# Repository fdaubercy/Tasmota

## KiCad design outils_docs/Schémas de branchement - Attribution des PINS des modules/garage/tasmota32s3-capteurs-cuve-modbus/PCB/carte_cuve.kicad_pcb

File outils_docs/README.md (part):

<hr></hr>

**Vous trouverez ici la méthodologie de développement de scripts en langage BERRY pour tasmota.<br/> Les différents devices développéespour la domotique du domicile sont des forks de Tasmota personnalisés.**

<hr></hr>

> [!TIP]
> ## Index de la documentation du dépôt
> Point d'entrée unique : chaque document du fork est listé ici. Les documents restent à
> l'endroit qu'impose leur outil (Claude Code, scripts qui les génèrent) ; seul cet index les réunit.
> Les fichiers marqués *(généré)* se régénèrent par leur script : ne pas les éditer à la main.

### Règles et chantiers
- [CLAUDE.md](../CLAUDE.md) — règles du dépôt, synchro du fork, montage d'un nouveau poste, vigilances de build, charte des logs.
- [tasks/lessons.md](../tasks/lessons.md) — journal des erreurs commises et règles qui en découlent (à relire avant de coder).
- [tasks/reprise-chantier-modbus-grenier.md](../tasks/reprise-chantier-modbus-grenier.md) — chantier ModBus (⚠️ cibles = les 3 modules du **garage**, malgré le nom).
- [tasks/reprise-solidification-berry.md](../tasks/reprise-solidification-berry.md) — chantier de solidification Berry.
- **Organigramme des plans, en ligne : <https://fdaubercy.github.io/Tasmota/organigramme.html>** — les 48 plans de `tasks/plans/` par famille, avec dates, avancement et liens ; mise à jour : [section dédiée](#organigramme-des-plans-page-web-et-powerpoint).

### Berry
- [SOLIDIFICATION_BERRY.md](SOLIDIFICATION_BERRY.md) — la solidification Berry : fonctionnement, **vérification**, paramètres, 13 pièges.
  À retenir : la ligne `Berry solidification: …` d'un build **ne prouve rien** (§5).
- [CARTE_MODULES_BERRY.md](CARTE_MODULES_BERRY.md) *(généré)* — module × carte : solidifié, importé, dépendance, garde du persist, incohérences.
- [Les logs Berry : charte et réglages](#les-logs-berry--charte-et-réglages) — plus bas dans ce fichier.
- [Inclinaison d'un volet ou d'une trappe (MPU6050)](#inclinaison-dun-volet-ou-dune-trappe-mpu6050) — capteur de position par l'angle, apprentissage des butées.
- Conception de la solidification : [design](../docs/superpowers/specs/2026-07-15-solidification-berry-design.md),
  [verdict](../docs/superpowers/specs/2026-07-15-solidification-berry-verdict.md),
  [plan de la phase 1](../docs/superpowers/plans/2026-07-15-solidification-berry-phase1.md).

### ModBus et réseau
- [PROTOCOLE_MODBUS.md](PROTOCOLE_MODBUS.md) — référence de **conception** : TCP, 3 transports, file d'envoi, registres de la carte 16 relais (§8), synchronisation maître/esclave (§9).
- [Aide/MODBUS.md](Aide/MODBUS.md) — **mode d'emploi** : commandes d'exemple (carte 16 relais, esclaves Tasmota), trames détaillées par code de fonction, activation dans Tasmota.
- [ANALYSE_BERRY_MODBUS_DISCOVERY.md](ANALYSE_BERRY_MODBUS_DISCOVERY.md) — programmes ModBus Berry et table `/json/discovery.json`.
- [AUDIT_MODBUS_2026-09-29.md](AUDIT_MODBUS_2026-09-29.md) — audit ModBus du garage (défauts, améliorations par priorité).

### Configuration des cartes et électronique
- [schemas/persist.schema.json](schemas/persist.schema.json) *(généré)* — schéma des `_persist.json` (autocomplétion et contrôle dans VS Code).
- [Electronique/ADS1115/CABLAGE_ADS1115.md](Electronique/ADS1115/CABLAGE_ADS1115.md) — câblage de l'ADS1115 (cuve).
- [Electronique/ADS1115/CABLAGE_RUBAN_LED.md](Electronique/ADS1115/CABLAGE_RUBAN_LED.md) — câblage du ruban LED.
- PCB : la skill [pcb-tasmota](../.claude/skills/pcb-tasmota/SKILL.md) et ses agents
  [placeur-pcb](../.claude/agents/placeur-pcb.md) / [relecteur-pcb](../.claude/agents/relecteur-pcb.md).

### Outils et historique
- [scripts_python/](scripts_python/) — outillage PC, rangé par usage : `build/`, `outils_pc/`, `berry/`, `maintenance/`, `sauvegarde/`, `reseau/` (détail dans [CLAUDE.md](../CLAUDE.md)).
- [HISTORIQUE_SYNCHRO_FORK.md](HISTORIQUE_SYNCHRO_FORK.md) *(généré)* — journal des synchronisations du fork.
- [CHANGELOG.md](CHANGELOG.md) — historique des évolutions.
- [Les graphiques des mesures](#les-graphiques-des-mesures-cartes-s3p4) — page `/graphiques` des cartes S3/P4, plus bas dans ce fichier.
- [Build et téléversement (page web)](#build-et-téléversement-page-web) — compiler et téléverser les cartes (COM ou OTA) depuis http://127.0.0.1:7700, plus bas dans ce fichier.
- [Fichiers Berry par env (page web)](#fichiers-berry-par-env-page-web) — sur le FS, exclu ou solidifié, et création d'un env, depuis http://127.0.0.1:7800, plus bas dans ce fichier.
- [Synchro du fork (page web)](#synchro-du-fork-page-web) — diagnostic et assistant pas à pas pour rattraper l'amont, depuis http://127.0.0.1:7500, plus bas dans ce fichier.
- [Sniffeur I2C (page web)](#sniffeur-i2c-page-web) — voir le trafic d'un bus I2C, décodé jusqu'au registre, par un ESP32-S3 dédié, depuis http://127.0.0.1:7350, plus bas dans ce fichier.

<hr></hr>

## Les logs Berry : charte et réglages

Le mécanisme vit dans `data/fs/logFonctions.be`, qui porte la même charte en tête.

### Les 4 niveaux

| Mot | Constante | Quand l'utiliser |
|---|---|---|
| `erreur` | `LOG_LEVEL_ERREUR` (1) | Un échec qui demande d'agir : exception, trame rejetée, abandon après N tentatives. **Toujours affiché**, quel que soit le réglage du module. |
| `info` | `LOG_LEVEL_INFO` (2) | Un événement ou un changement d'état, une ligne par événement : relais commuté, esclave connecté, configuration appliquée. |
| `debug` | `LOG_LEVEL_DEBUG` (3) | Le déroulé d'un traitement : étapes, décisions, valeurs clés. |
| `detail` | `LOG_LEVEL_DEBUG_PLUS` (4) | Le brut : trames, JSON complets, paramètres reçus. Sort au niveau 3 de Tasmota, sans les `BRY: GC`. |

Dans le code : toujours `logFonctions.log(msg, niveau [, cible])`, jamais `log()` directement.
Un échec se logue en `erreur`, jamais en `debug`. Pas d'`info` dans un traitement répété
(toutes les secondes, à chaque trame reçue, à chaque affichage de la page : `web_sensor`, `json_append`).
Un message coûteux (`json.dump`, `tohex`) se construit seulement si `logFonctions.actif(...)` est vrai.
Le niveau s'écrit par sa constante `LOG_LEVEL_*`, jamais en chiffre ; un niveau variable passe par
l'enrobeur du module (`xxxFonctions.log(msg, niveau)`) ou par une ternaire entre constantes.
`verifie_berry.py` signale les écarts à ces règles en avertissements, sans bloquer.

### Deux filtres successifs

Un message n'est affiché que s'il passe les deux :

1. **Le réglage de son module** (la *cible*) : `general`, `serveurWeb`, `udp`, `tcp`, `rangeExtender`,
   `discovery`, `modbus`, `conn16channels`, `slaveModbus`, `lorawan`, `volets`, `es8311`,
   `garage`, `cuve`, `rideau`, `leds`, `historique` (S3/P4 avec historique local), `ecranCave` et
   `ecranDebits` (cartes à écran ; `ecranCave` aussi sur le serveur de la cave, pour ses touches).
   (`web` désigne la **sortie** console web ; le module des pages web est `serveurWeb`.)
2. **Le réglage de la sortie** : `serie`, `web`, `mqtt` (topic `stat/<topic>/LOGGING`),
   `syslog` (le PC, `syslog_tasmota.py`). Ces réglages forment un **profil**.

Exemple : pour voir les trames ModBus dans la console, il faut `ReglageLog modbus detail`
**et** un profil dont la sortie `serie` est au moins à `debug`.

### Les commandes

```
ReglageLog                          affiche le profil actif, les sorties et le réglage de chaque module
ReglageLog help                     liste les sous-commandes (aide affichée en console)
ReglageLog help modbus              détail d'une sous-commande, avec le réglage actuel (help niveaux : la charte)
ReglageLog profil debug             applique le profil « debug » (ou « normal ») aux sorties
ReglageLog modbus debug             règle le module ModBus : erreur | info | debug | detail
ReglageLog tous detail              règle d'un coup tous les modules présents sur la carte
ReglageLog syslog info              règle une sortie du profil actif : aucun | erreur | info | debug | detail
```

Tout est enregistré dans `_persist.json`. Une sortie à `detail` affiche aussi les lignes
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
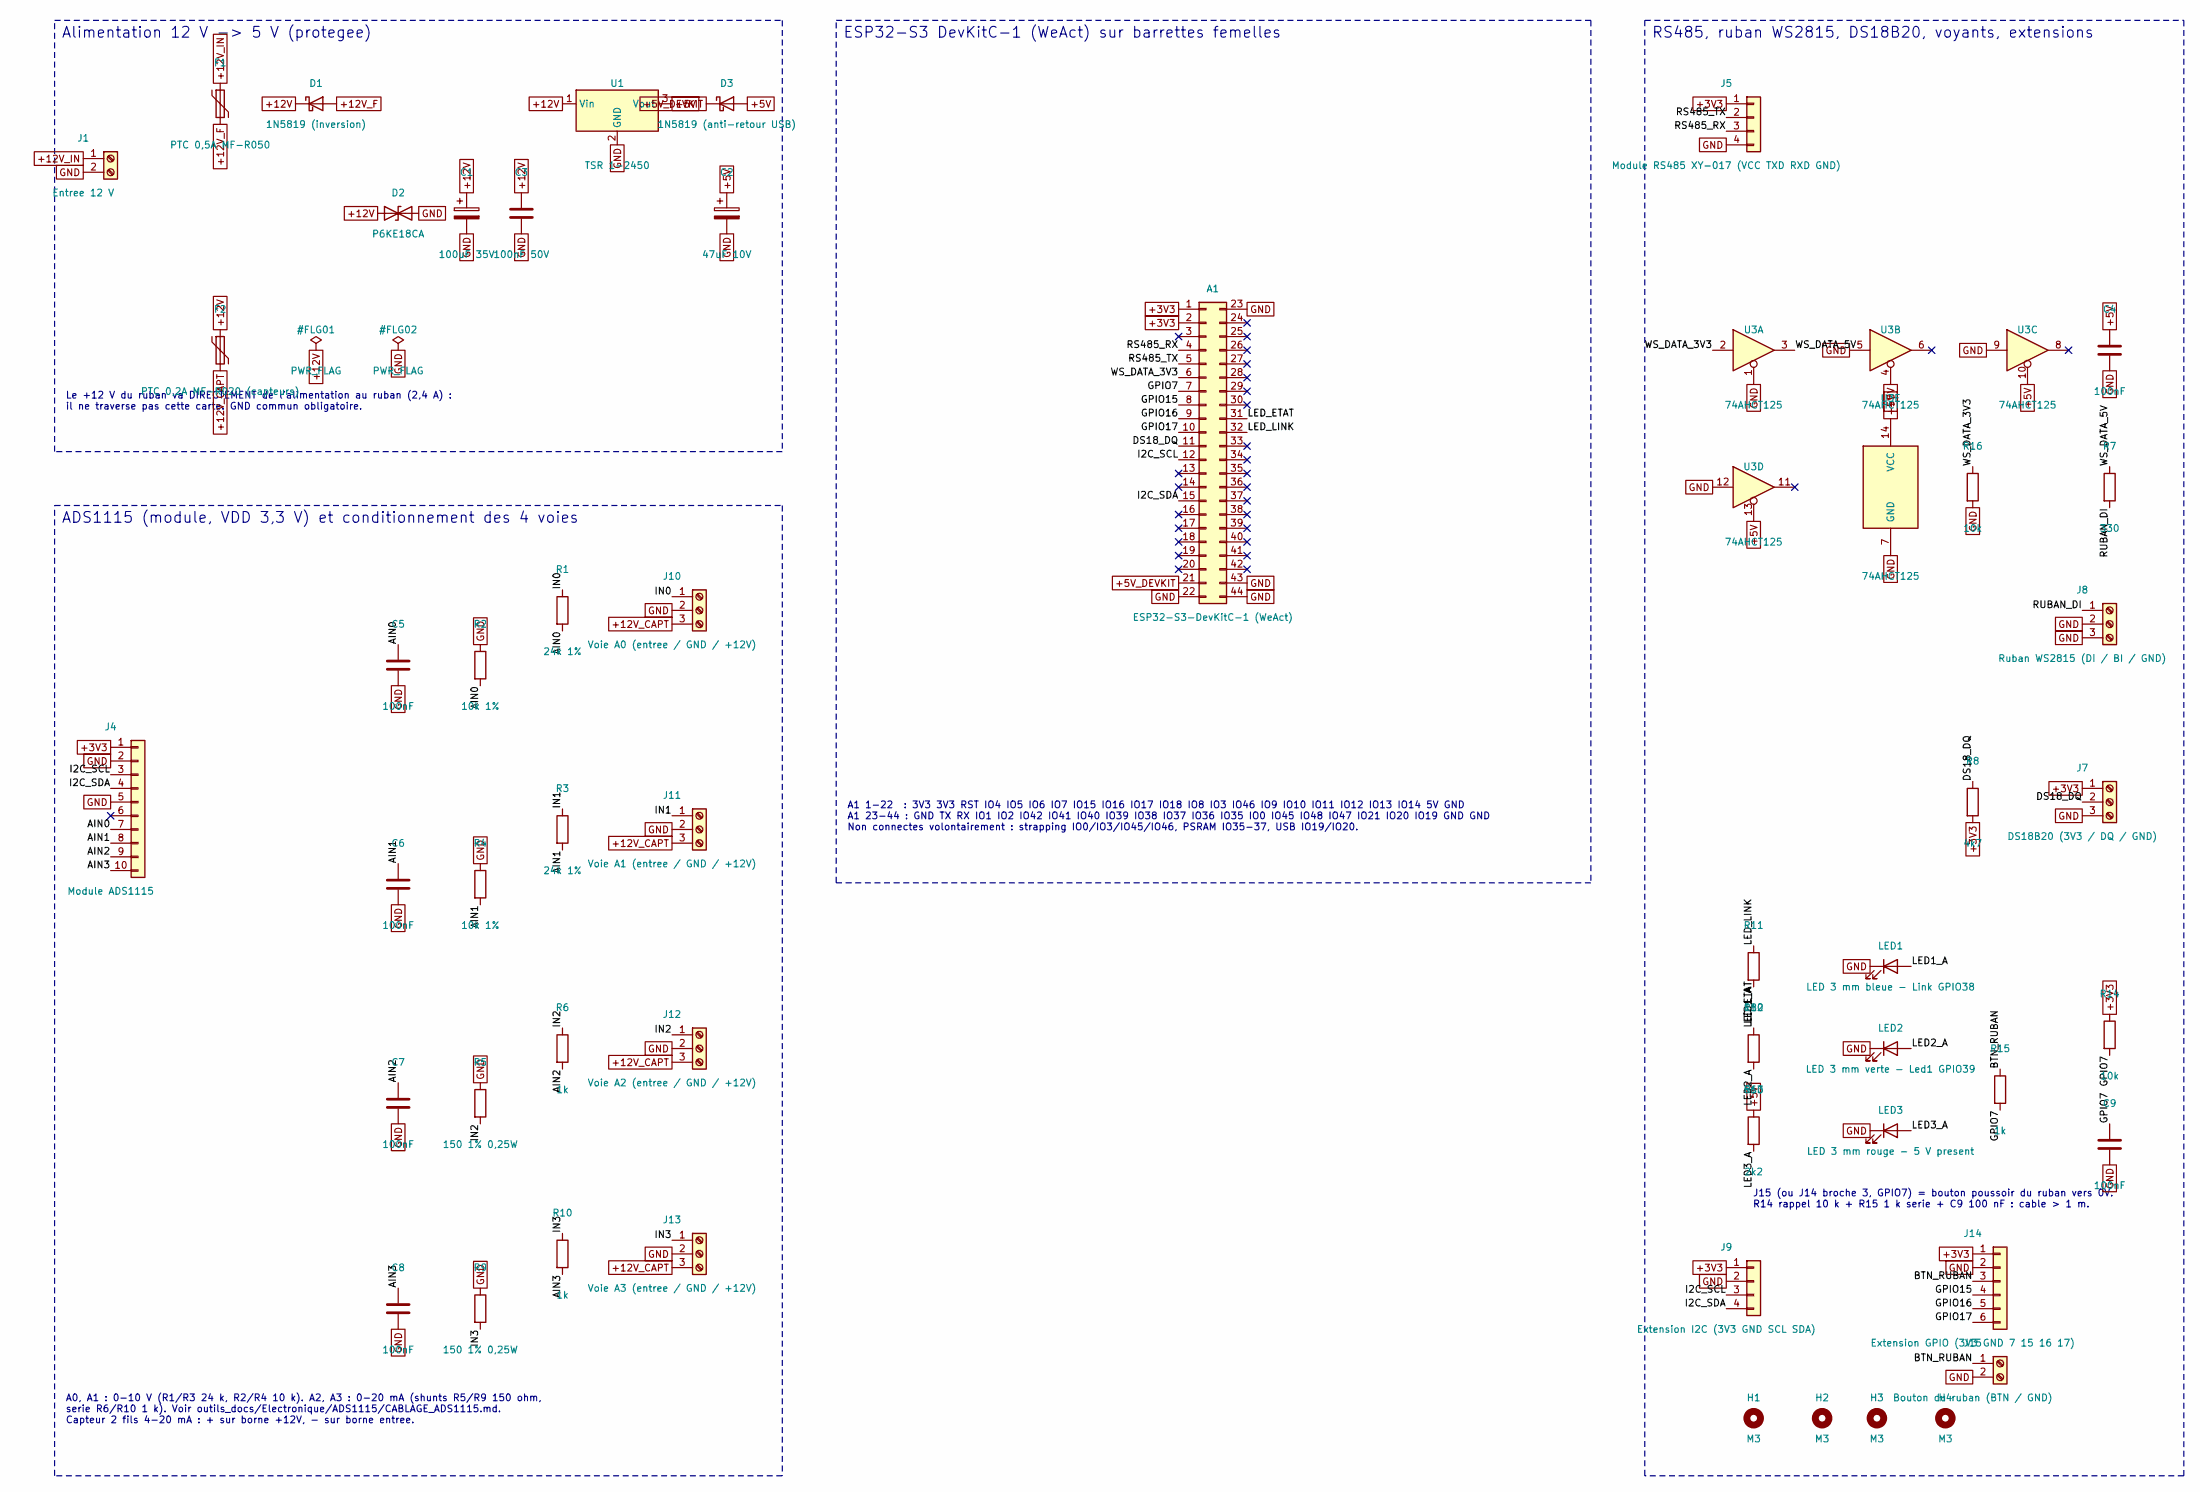
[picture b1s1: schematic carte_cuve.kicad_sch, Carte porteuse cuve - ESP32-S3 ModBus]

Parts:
A1: ESP32-S3-DevKitC-1 (WeAct); ESP32-S3-DevKitC-1_E25.40mm
C1: 100uF 35V; CP_Radial_D8.0mm_P3.50mm
C2: 47uF 10V; CP_Radial_D5.0mm_P2.00mm
C3: 100nF 50V; C_Disc_D3.0mm_W1.6mm_P2.50mm
C4, C5, C6, C7, C8, C9: 100nF; C_Disc_D5.0mm_W2.5mm_P5.00mm
D1: 1N5819 (inversion); D_DO-41_SOD81_P10.16mm_Horizontal
D2: P6KE18CA; D_DO-15_P10.16mm_Horizontal
D3: 1N5819 (anti-retour USB); D_DO-41_SOD81_P10.16mm_Horizontal
F1: PTC 0,5A MF-R050; Fuse_Bourns_MF-RHT050
F2: PTC 0,2A MF-R020 (capteurs); Fuse_Bourns_MF-RHT050
H1, H2, H3, H4: M3; MountingHole_3.2mm_M3
J1: Entree 12 V; TerminalBlock_Phoenix_MKDS-1,5-2-5.08_1x02_P5.08mm_Horizont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
J4: Module ADS1115; Module_ADS1115_1x10
J5: Module RS485 XY-017 (VCC TXD RXD GND); Module_RS485_Auto_XY-017
J7: DS18B20 (3V3 / DQ / GND); TerminalBlock_Phoenix_MKDS-1,5-3-5.08_1x03_P5.08mm_Horizont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
J8: Ruban WS2815 (DI / BI / GND); TerminalBlock_Phoenix_MKDS-1,5-3-5.08_1x03_P5.08mm_Horizont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
J9: Extension I2C (3V3 GND SCL SDA); PinHeader_1x04_P2.54mm_Vertical
J10: Voie A0 (entree / GND / +12V); TerminalBlock_Phoenix_MKDS-1,5-3-5.08_1x03_P5.08mm_Horizont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
J11: Voie A1 (entree / GND / +12V); TerminalBlock_Phoenix_MKDS-1,5-3-5.08_1x03_P5.08mm_Horizont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
J12: Voie A2 (entree / GND / +12V); TerminalBlock_Phoenix_MKDS-1,5-3-5.08_1x03_P5.08mm_Horizont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
J13: Voie A3 (entree / GND / +12V); TerminalBlock_Phoenix_MKDS-1,5-3-5.08_1x03_P5.08mm_Horizont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
J14: Extension GPIO (3V3 GND 7 15 16 17); PinHeader_1x06_P2.54mm_Vertical
J15: Bouton du ruban (BTN / GND); TerminalBlock_Phoenix_MKDS-1,5-2-5.08_1x02_P5.08mm_Horizont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
LED1: LED 3 mm bleue - Link GPIO38; LED_D3.0mm
LED2: LED 3 mm verte - Led1 GPIO39; LED_D3.0mm
LED3: LED 3 mm rouge - 5 V present; LED_D3.0mm
R1, R3: 24k 1%; R_Axial_DIN0207_L6.3mm_D2.5mm_P10.16mm_Horizontal
R2, R4: 10k 1%; R_Axial_DIN0207_L6.3mm_D2.5mm_P10.16mm_Horizontal
R5, R9: 150 1% 0,25W; R_Axial_DIN0207_L6.3mm_D2.5mm_P10.16mm_Horizontal
R6, R10: 1k; R_Axial_DIN0207_L6.3mm_D2.5mm_P10.16mm_Horizontal
R7: 330; R_Axial_DIN0207_L6.3mm_D2.5mm_P10.16mm_Horizontal
R8: 4k7; R_Axial_DIN0207_L6.3mm_D2.5mm_P2.54mm_Vertical
R11: 180; R_Axial_DIN0207_L6.3mm_D2.5mm_P2.54mm_Vertical
R12: 560; R_Axial_DIN0207_L6.3mm_D2.5mm_P2.54mm_Vertical
R13: 2k2; R_Axial_DIN0207_L6.3mm_D2.5mm_P2.54mm_Vertical
R14: 10k; R_Axial_DIN0207_L6.3mm_D2.5mm_P10.16mm_Horizontal
R15: 1k; R_Axial_DIN0207_L6.3mm_D2.5mm_P2.54mm_Vertical
R16: 10k; R_Axial_DIN0207_L6.3mm_D2.5mm_P2.54mm_Vertical
U1: TSR 1-2450; Converter_DCDC_TRACO_TSR-1_THT
U3: 74AHCT125; DIP-14_W7.62mm

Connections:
+3V3: A1.1, A1.2, J4.1, J5.1, J7.1, J9.1, J14.1, R8.2, R14.1
+5V: C2.1, C4.1, D3.2 (A), R13.1, U1.3 (Vout), U3.4, U3.10, U3.13, U3.14 (VCC)
+5V_DEVKIT: A1.21, D3.1 (K)
+12V: C1.1, C3.1, D1.1 (K), D2.1 (A1), F2.1, U1.1 (Vin)
+12V_CAPT: F2.2, J10.3, J11.3, J12.3, J13.3
+12V_F: D1.2 (A), F1.2
+12V_IN: F1.1, J1.1
/AIN0: C5.1, J4.7, R1.2, R2.2
/AIN1: C6.1, J4.8, R3.2, R4.2
/AIN2: C7.1, J4.9, R6.2
/AIN3: C8.1, J4.10, R10.2
/BTN_RUBAN: J14.3, J15.1, R15.1
/DS18_DQ: A1.11, J7.2, R8.1
/GPIO7: A1.7, C9.1, R14.2, R15.2
/GPIO15: A1.8, J14.4
/GPIO16: A1.9, J14.5
/GPIO17: A1.10, J14.6
/I2C_SCL: A1.12, J4.3, J9.3
/I2C_SDA: A1.15, J4.4, J9.4
/IN0: J10.1, R1.1
/IN1: J11.1, R3.1
/IN2: J12.1, R5.2, R6.1
/IN3: J13.1, R9.2, R10.1
/LED1_A: LED1.2 (A), R11.2
/LED2_A: LED2.2 (A), R12.2
/LED3_A: LED3.2 (A), R13.2
/LED_ETAT: A1.31, R12.1
/LED_LINK: A1.32, R11.1
/RS485_RX: A1.4, J5.3
/RS485_TX: A1.5, J5.2
/RUBAN_DI: J8.1, R7.2
/WS_DATA_3V3: A1.6, R16.1, U3.2
/WS_DATA_5V: R7.1, U3.3
GND: A1.22, A1.23, A1.43, A1.44, C1.2, C2.2, C3.2, C4.2, C5.2, C6.2, C7.2, C8.2, C9.2, D2.2 (A2), J1.2, J4.2, J4.5, J5.4, J7.3, J8.2, J8.3, J9.2, J10.2, J11.2, J12.2, J13.2, J14.2, J15.2, LED1.1 (K), LED2.1 (K), LED3.1 (K), R2.1, R4.1, R5.1, R9.1, R16.2, U1.2 (GND), U3.1, U3.5, U3.7 (GND), U3.9, U3.12

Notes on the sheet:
Alimentation 12 V -> 5 V (protegee)
Le +12 V du ruban va DIRECTEMENT de l'alimentation au ruban (2,4 A) : il ne traverse pas cette carte. GND commun obligatoire.
ESP32-S3 DevKitC-1 (WeAct) sur barrettes femelles
A1 1-22 : 3V3 3V3 RST IO4 IO5 IO6 IO7 IO15 IO16 IO17 IO18 IO8 IO3 IO46 IO9 IO10 IO11 IO12 IO13 IO14 5V GND A1 23-44 : GND TX RX IO1 IO2 IO42 IO41 IO40 IO39 IO38 IO37 IO36 IO35 IO0 IO45 IO48 IO47 IO21 IO20 IO19 GND GND Non connectes volontairement : strapping IO0/IO3/IO45/IO46, PSRAM IO35-37, USB IO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
ADS1115 (module, VDD 3,3 V) et conditionnement des 4 voies
A0, A1 : 0-10 V (R1/R3 24 k, R2/R4 10 k). A2, A3 : 0-20 mA (shunts R5/R9 150 ohm, serie R6/R10 1 k). Voir outils_docs/Electronique/ADS1115/CABLAGE_ADS1115.md. Capteur 2 fils 4-20 mA : + sur borne +12V, - sur borne entree.
RS485, ruban WS2815, DS18B20, voyants, extensions
J15 (ou J14 broche 3, GPIO7) = bouton poussoir du ruban vers 0V. R14 rappel 10 k + R15 1 k serie + C9 100 nF : cable > 1 m.

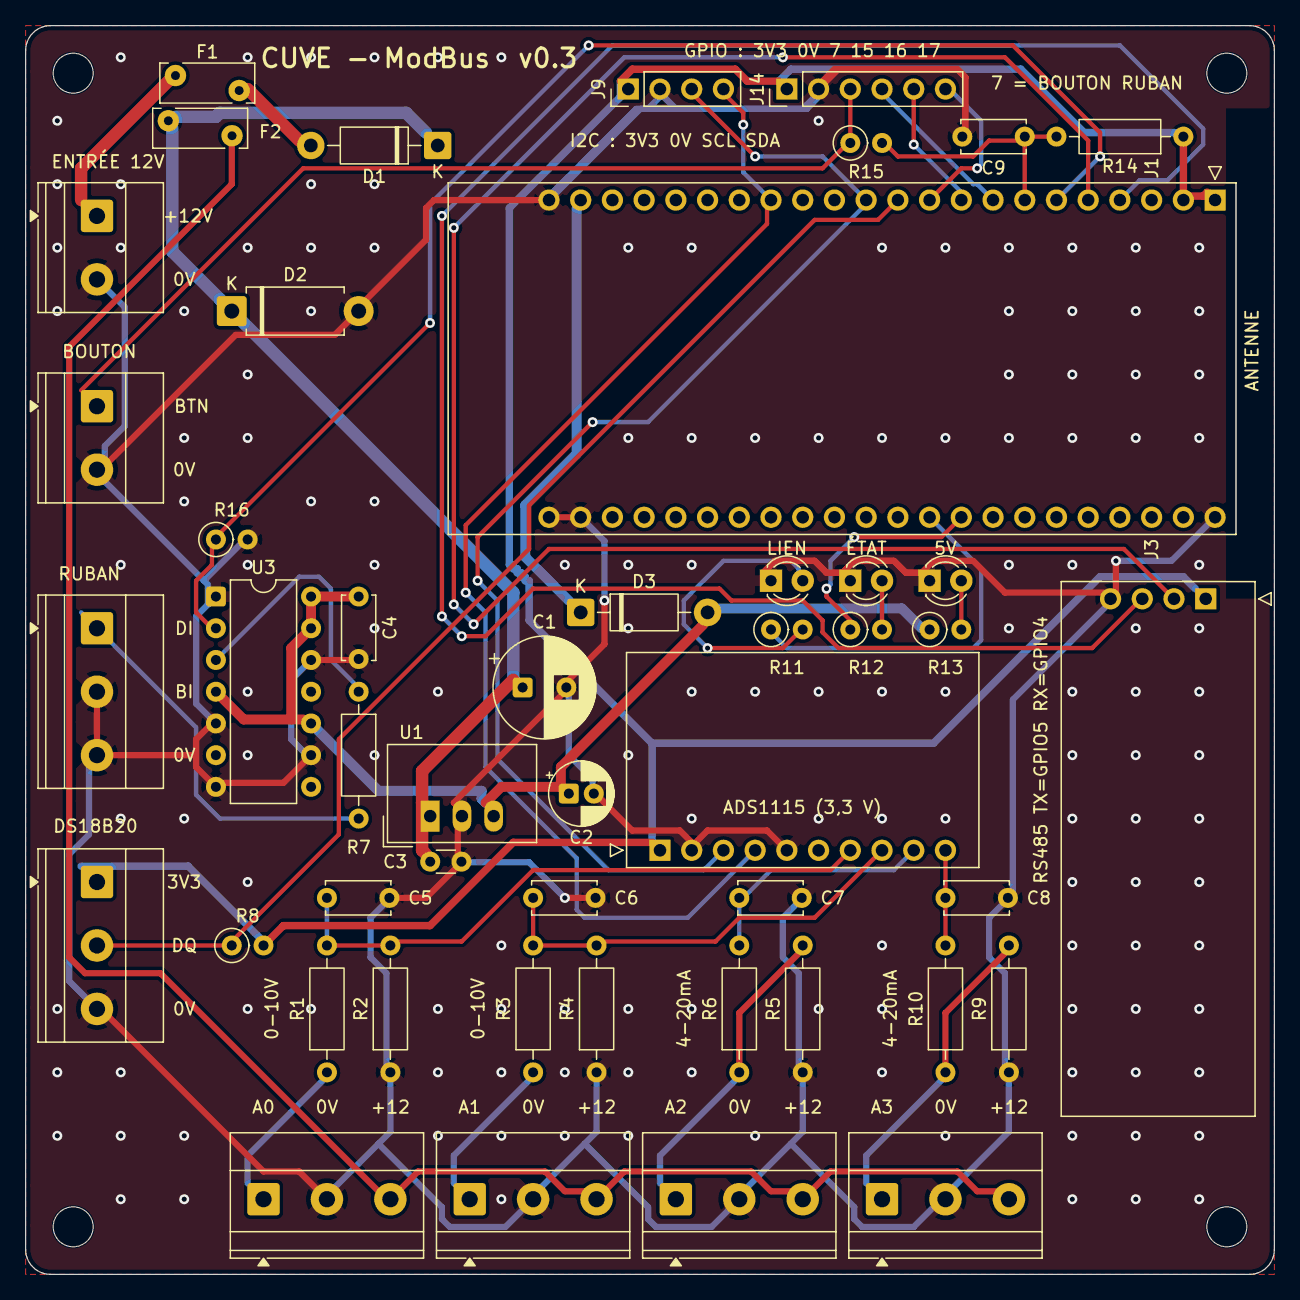
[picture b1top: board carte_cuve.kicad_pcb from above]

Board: 2 copper layers, 100.0 x 100.0 mm, 53 parts (0 on the bottom side), 34 nets.

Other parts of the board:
LOGO1: Signature_Auteur_30mm_Dos

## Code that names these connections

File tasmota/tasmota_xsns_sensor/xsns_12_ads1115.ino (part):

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#define ADS1115_REG_CONFIG_OS_NOTBUSY   (0x8000)  // Read: Bit = 1 when device is not performing a conversion

#define ADS1115_REG_CONFIG_MUX_MASK     (0x7000)
#define ADS1115_REG_CONFIG_MUX_DIFF_0_1 (0x0000)  // Differential P = AIN0, N = AIN1 (default)
#define ADS1115_REG_CONFIG_MUX_DIFF_0_3 (0x1000)  // Differential P = AIN0, N = AIN3
#define ADS1115_REG_CONFIG_MUX_DIFF_1_3 (0x2000)  // Differential P = AIN1, N = AIN3
#define ADS1115_REG_CONFIG_MUX_DIFF_2_3 (0x3000)  // Differential P = AIN2, N = AIN3
#define ADS1115_REG_CONFIG_MUX_SINGLE_0 (0x4000)  // Single-ended AIN0
#define ADS1115_REG_CONFIG_MUX_SINGLE_1 (0x5000)  // Single-ended AIN1
#define ADS1115_REG_CONFIG_MUX_SINGLE_2 (0x6000)  // Single-ended AIN2
#define ADS1115_REG_CONFIG_MUX_SINGLE_3 (0x7000)  // Single-ended AIN3

#define ADS1115_REG_CONFIG_PGA_MASK     (0x0E00)
#define ADS1115_REG_CONFIG_PGA_6_144V   (0x0000)  // +/-6.144V range = Gain 2/3 (default)
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

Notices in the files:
tasmota/tasmota_xsns_sensor/xsns_12_ads1115.ino:
Copyright (C) 2021  Syssi, stefanbode
This program is free software: you can redistribute it and/or modify
it under the terms of the GNU General Public License as published by
the Free Software Foundation, either version 3 of the License, or
(at your option) any later version.
outils_docs/README.md:
permissives passent, les CC BY demandent une confirmation d'attribution à la conservation, le reste est masqué.
